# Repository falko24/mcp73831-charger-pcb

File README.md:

Kompaktowa, jednocelowa płytka zarządzania i ładowania akumulatorów Li-Ion/Li-Po zaprojektowana od zera w programie KiCad. Projekt opiera się na popularnym układzie liniowej kontroli ładowania **MCP73831** oraz wykorzystuje nowoczesne gniazdo zasilania **USB typu C**.

## 📸 Podgląd Płytki (PCB)

| Przód (Top) | Tył (Bottom) |
| :---: | :---: |
|  |  |

## 🚀 Funkcje
* **Złącze USB-C:** Skonfigurowane z odpowiednimi rezystorami ściągającymi na liniach CC dla standardowej negocjacji zasilania.
* **Inteligentne ładowanie:** Układ MCP73831 firmy Microchip zapewnia bezpieczny, regulowany cykl ładowania dla jednocelowych akumulatorów litowych.
* **Sygnalizacja stanu:** Wbudowana wskaźnikowa dioda LED do monitorowania procesu ładowania.
* **Kompaktowy rozmiar:** Czysty routing i zoptymalizowany układ ścieżek dostosowany do celów hobbystycznych oraz edukacyjnych.

## 🛠️ Narzędzia i Technologie
* **Oprogramowanie EDA:** KiCad (Edytor schematów i płytek PCB)
* **Kluczowe komponenty:**
  * `MCP73831` (Kontroler ładowania Li-Ion/Li-Po w obudowie SOT-23-5)
  * Gniazdo **USB-C** (interfejs 14-pinowy)
  * Standardowe elementy bierne do montażu powierzchniowego (SMD)

## 📂 Struktura Repozytorium
```text
├── 📁 docs/              # Dokumentacja graficzna (zdjęcia płytki)
├── 📁 gerber/           # Gotowe pliki produkcyjne Gerber i wiercenia
├── 📁 schematics/        # Pliki schematów KiCad (.kicad_sch)
├── 📁 pcb/               # Pliki projektu płytki PCB (.kicad_pcb)
└── README.md             # Dokumentacja projektu

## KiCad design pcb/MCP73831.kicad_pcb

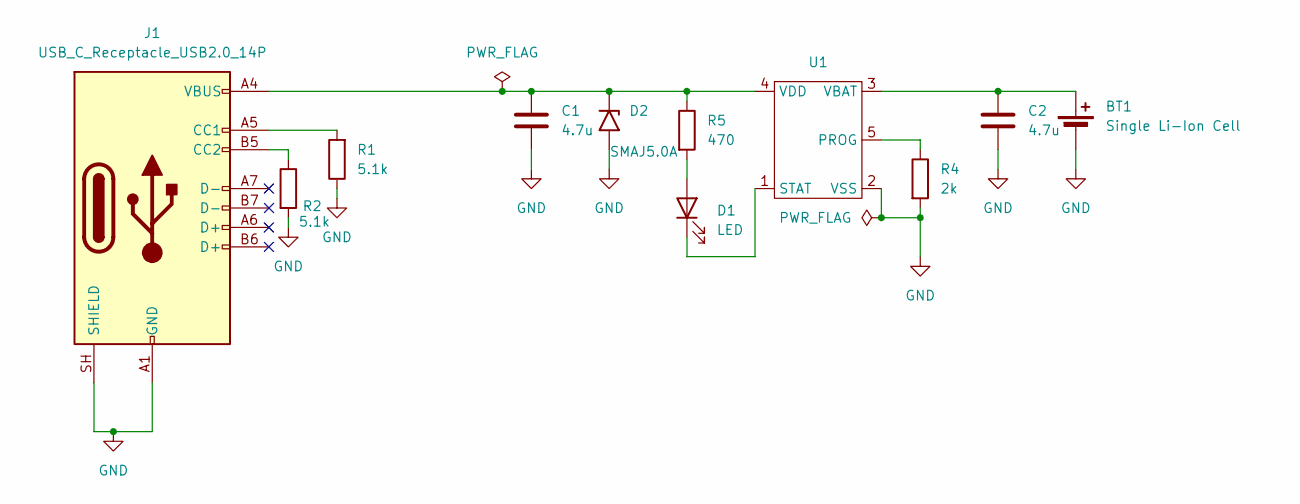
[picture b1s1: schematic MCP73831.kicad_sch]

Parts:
BT1: Single Li-Ion Cell; JST_PH_B2B-PH-K_1x02_P2.00mm_Vertical
C1, C2: 4.7u; C_1206_3216Metric
D1: LED; LED_1206_3216Metric
D2: SMAJ5.0A; D_SMA
J1: USB_C_Receptacle_USB2.0_14P; USB_C_Receptacle_HCTL_HC-TYPE-C-16P-01A
R1, R2: 5.1k; R_1206_3216Metric
R4: 2k; R_1206_3216Metric
R5: 470; R_1206_3216Metric
U1: TSOT-23-5_HandSoldering

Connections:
GND: BT1.2 (-), C1.2, C2.2, D2.2 (A2), J1.A1 (GND), J1.A12 (GND), J1.B1 (GND), J1.B12 (GND), J1.SH (SHIELD), R1.1, R2.2, R4.2, U1.2 (VSS)
unnamed: BT1.1 (+), C2.1, U1.3 (VBAT)
unnamed: D1.2 (A), R5.2
unnamed: D1.1 (K), U1.1 (STAT)
unnamed: C1.1, D2.1 (A1), J1.A4 (VBUS), J1.A9 (VBUS), J1.B4 (VBUS), J1.B9 (VBUS), R5.1, U1.4 (VDD)
unnamed: J1.A5 (CC1), R1.2
unnamed: J1.B5 (CC2), R2.1
unnamed: R4.1, U1.5 (PROG)

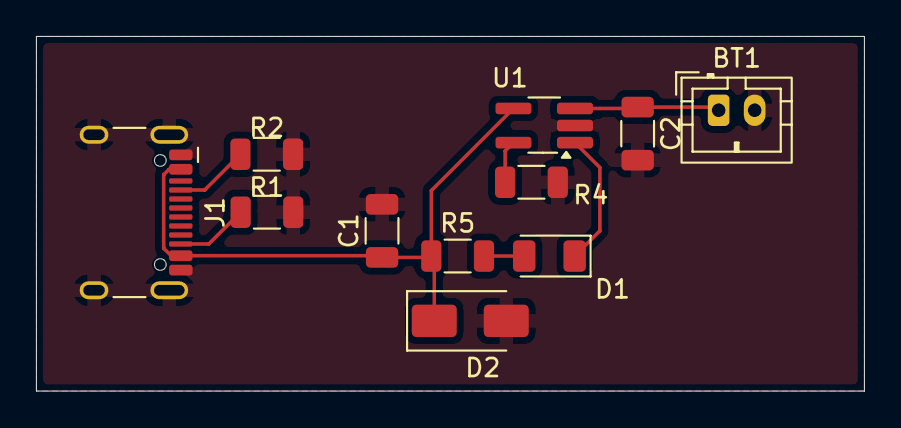
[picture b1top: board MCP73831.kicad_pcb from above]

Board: 2 copper layers, 46.0 x 19.7 mm, 11 parts (0 on the bottom side), 8 nets.
